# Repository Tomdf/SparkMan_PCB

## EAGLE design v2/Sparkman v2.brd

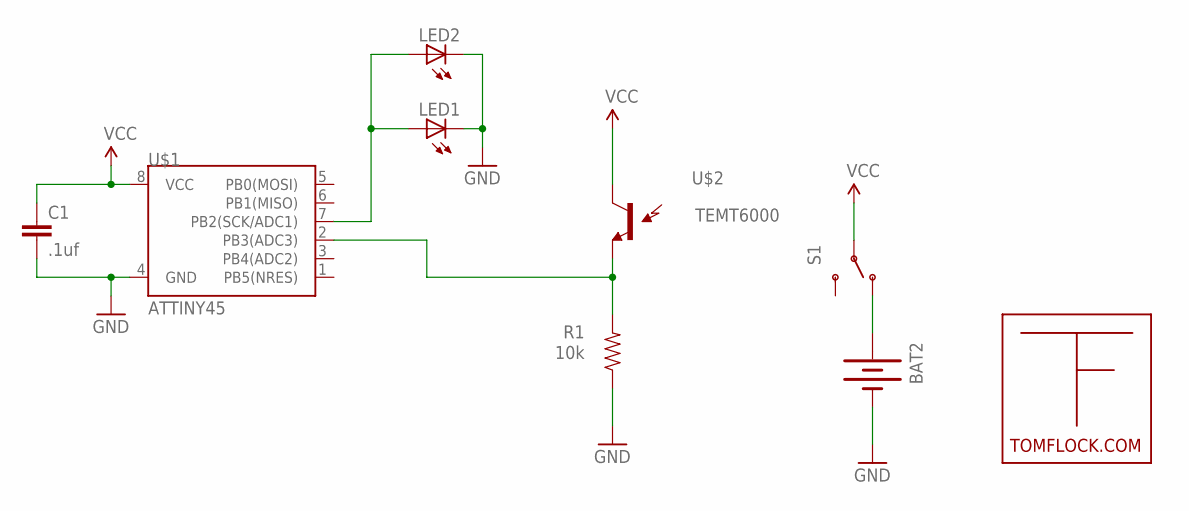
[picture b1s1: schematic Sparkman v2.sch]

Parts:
BAT2: BATTERY12MM; BATTCON_12MM
C1: .1uf; 0603-CAP
LED1, LED2: LED0603; LED-0603
R1: 10k; 0603-RES
S1: SWITCH-SPSTSMD; AYZ0202
U$1: ATTINY45; SO08-EIAJ
U$2: TEMT6000; TEMT6000-SEN
U$3: TFLOGO

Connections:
GND: BAT2.GND (-), C1.2, LED1.C, LED2.C, R1.1, U$1.4 (GND)
unnamed: LED1.A, LED2.A, U$1.7 (PB2(SCK/ADC1))
unnamed: R1.2, U$1.2 (PB3(ADC3)), U$2.EMITTER (E1)
unnamed: BAT2.PWR@1 (+), S1.1 (O)
VCC: C1.1, S1.2, U$1.8 (VCC), U$2.COLLECTOR (C1)

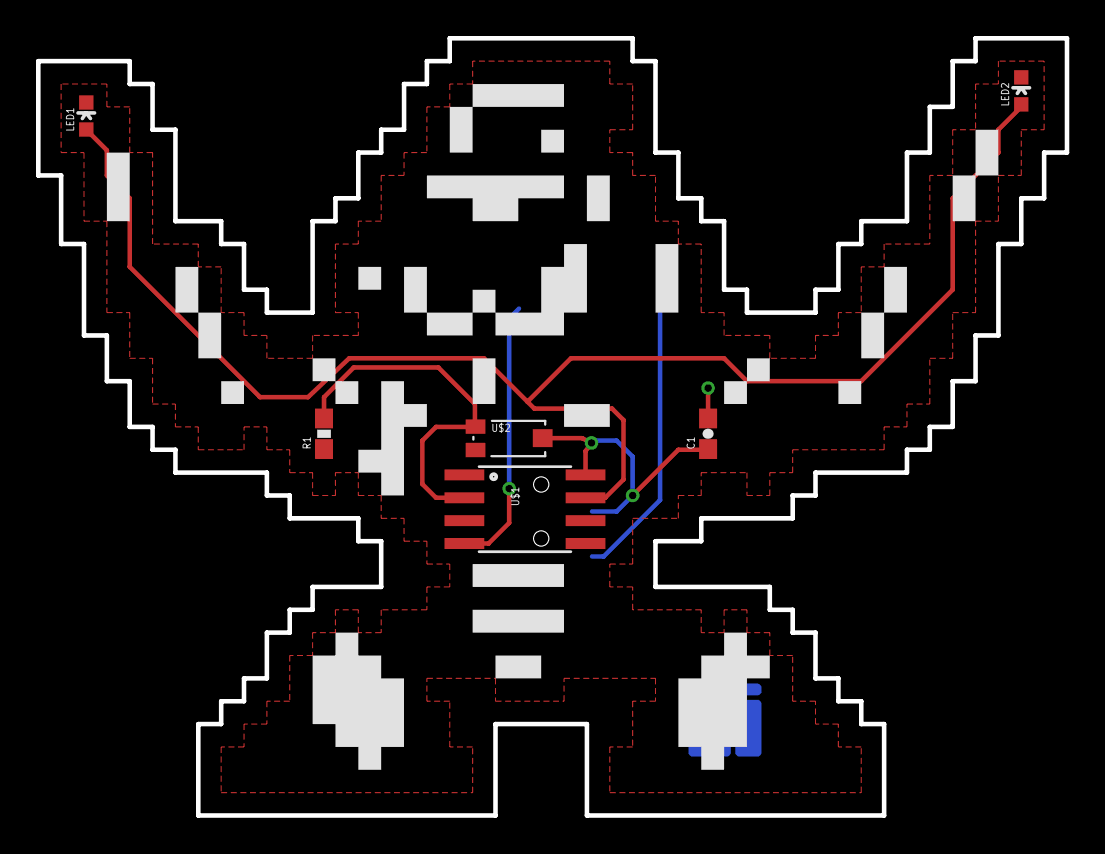
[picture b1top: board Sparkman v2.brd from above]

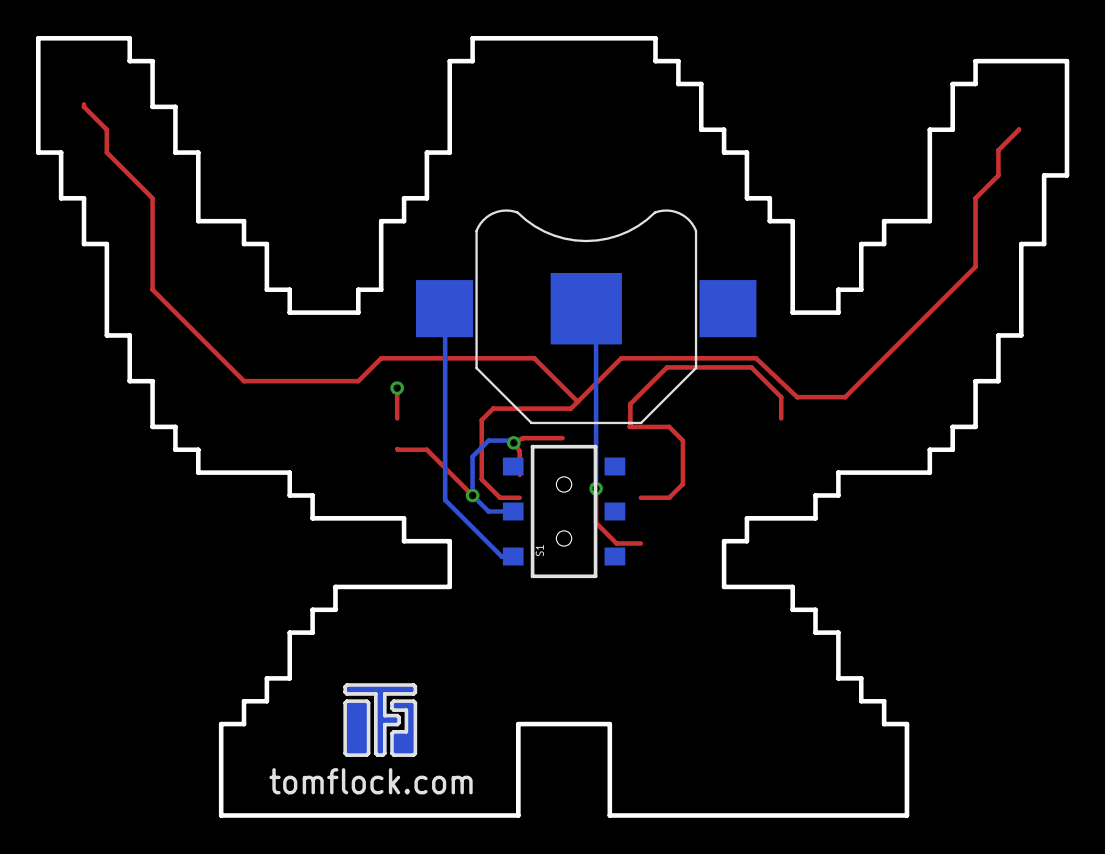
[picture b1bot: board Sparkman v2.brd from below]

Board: 2 copper layers, 57.2 x 43.2 mm, 9 parts (3 on the bottom side), 5 nets.

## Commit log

2013-09-09 Initial Commitzor
    Out of the frying pan, into the virtual storage space

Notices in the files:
parts and their libraries:
SparkFun: Licensing: CC v3.0 Share-Alike You are welcome to use this library for commercial purposes.
